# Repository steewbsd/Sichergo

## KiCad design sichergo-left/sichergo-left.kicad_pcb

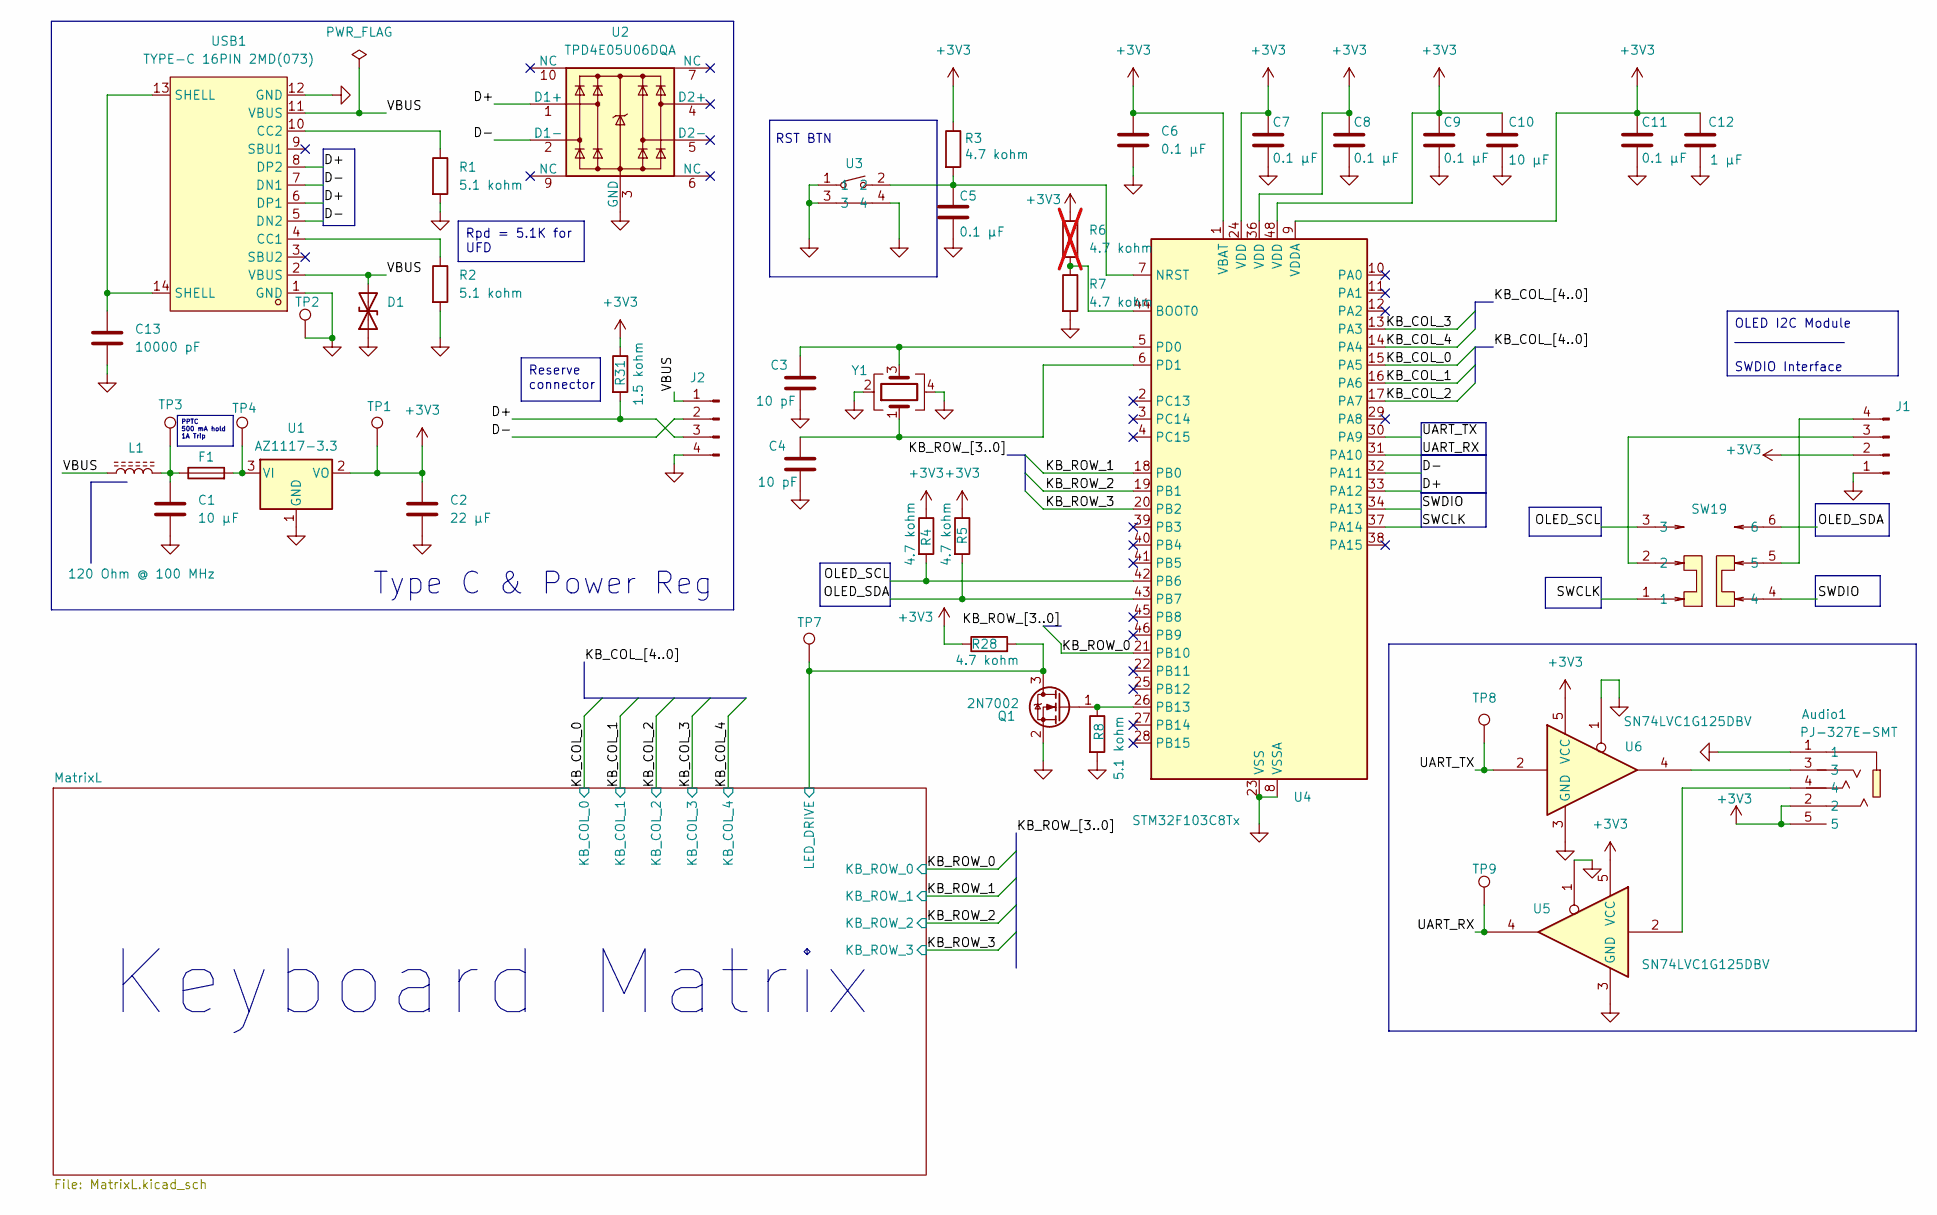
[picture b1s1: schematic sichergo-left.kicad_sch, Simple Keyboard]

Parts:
Audio1: PJ-327E-SMT; AUDIO-SMD_PJ-327E-SMT; LCSC Part C319105
C1, C10: 10 µF; C_0805_2012Metric_Pad1.18x1.45mm_HandSolder; Rated Voltage 16V; Tolerance 10%
C2: 22 µF; C_0805_2012Metric_Pad1.18x1.45mm_HandSolder; Rated Voltage 16V; Tolerance 20%
C3, C4: 10 pF; C_0805_2012Metric_Pad1.18x1.45mm_HandSolder; Rated Voltage 50V; Tolerance 0.25pF
C5, C6, C7, C8, C9, C11: 0.1 µF; C_0805_2012Metric_Pad1.18x1.45mm_HandSolder; Rated Voltage 50V; Tolerance 10%
C12: 1 µF; C_0805_2012Metric_Pad1.18x1.45mm_HandSolder; Rated Voltage 25V; Tolerance 10%
C13: 10000 pF; C_0805_2012Metric_Pad1.18x1.45mm_HandSolder; Rated Voltage 50V; Tolerance 10%
D1: CPDUR5V0HE-HF; D_0603_1608Metric_Pad1.05x0.95mm_HandSolder
F1: 1812L050/30PR; Fuse_1812_4532Metric_Pad1.30x3.40mm_HandSolder
J1: Conn_01x04_Pin; PinSocket_1x04_P2.54mm_Horizontal
J2: Conn_01x04_Pin; PinSocket_1x04_P2.54mm_Vertical
L1: 120 Ohm @ 100 MHz; L_0603_1608Metric_Pad1.05x0.95mm_HandSolder
Q1: 2N7002; SOT-23_Handsoldering
R1, R2, R8: 5.1 kohm; R_0603_1608Metric_Pad0.98x0.95mm_HandSolder; Tolerance 1%
R3, R4, R5, R7, R28: 4.7 kohm; R_0603_1608Metric_Pad0.98x0.95mm_HandSolder; Tolerance 1%
R6: 4.7 kohm; R_0603_1608Metric_Pad0.98x0.95mm_HandSolder; Tolerance 1%; not fitted
R31: 1.5 kohm; R_0603_1608Metric_Pad0.98x0.95mm_HandSolder; Tolerance 1%
SW19: MS-22C01-G010; SW-SMD_6P-L7.2-W3.5-P2.50-LS6.0-TL; LCSC Part C2837066
TP1, TP2, TP3, TP4, TP7, TP8, TP9: TestPoint; TestPoint_THTPad_1.0x1.0mm_Drill0.5mm
U1: AZ1117-3.3; SOT-223-3_TabPin2
U2: TPD4E05U06DQA; USON-10_2.5x1.0mm_P0.5mm
U3: YTS1C0033BBG01; SW-SMD_YIYUAN_YTS1C003XXX; LCSC Part C5188566
U4: STM32F103C8Tx; LQFP-48_7x7mm_P0.5mm
U5, U6: SN74LVC1G125DBV; SOT-23-5_HandSoldering
USB1: TYPE-C 16PIN 2MD(073); USB-C-SMD_TYPE-C-6PIN-2MD-073; LCSC Part C2765186
Y1: Crystal_GND24; Crystal_SMD_3225-4Pin_3.2x2.5mm_HandSoldering

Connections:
+3V3: Audio1.2, Audio1.5, C2.1, C6.1, C7.1, C8.1, C9.1, C10.1, C11.1, C12.1, J1.2, R3.1, R4.1, R5.1, R6.1, R28.1, R31.1, TP1.1, U1.2 (VO), U4.1 (VBAT), U4.9 (VDDA), U4.24 (VDD), U4.36 (VDD), U4.48 (VDD), U5.5 (VCC), U6.5 (VCC)
/D+: J2.3, R31.2, U2.1 (D1+), U4.33 (PA12), USB1.6 (DP1), USB1.8 (DP2)
/D-: J2.2, U2.2 (D1-), U4.32 (PA11), USB1.5 (DN2), USB1.7 (DN1)
/KB_COL_0: U4.15 (PA5); also elsewhere on the board
/KB_COL_1: U4.16 (PA6); also elsewhere on the board
/KB_COL_2: U4.17 (PA7); also elsewhere on the board
/KB_COL_3: U4.13 (PA3); also elsewhere on the board
/KB_COL_4: U4.14 (PA4); also elsewhere on the board
/KB_ROW_0: U4.21 (PB10); also elsewhere on the board
/KB_ROW_1: U4.18 (PB0); also elsewhere on the board
/KB_ROW_2: U4.19 (PB1); also elsewhere on the board
/KB_ROW_3: U4.20 (PB2); also elsewhere on the board
/MatrixL/LED_DRIVE: Q1.3 (D), R28.2, TP7.1; also elsewhere on the board
/OLED_SCL: R4.2, SW19.3, U4.42 (PB6)
/OLED_SDA: R5.2, SW19.6, U4.43 (PB7)
/SWCLK: SW19.1, U4.37 (PA14)
/SWDIO: SW19.4, U4.34 (PA13)
/UART_RX: TP9.1, U4.31 (PA10), U5.4
/UART_TX: TP8.1, U4.30 (PA9), U6.2
/VBUS: D1.2 (A2), J2.1, L1.1, USB1.2 (VBUS), USB1.11 (VBUS)
GND: Audio1.1, C1.2, C2.2, C3.2, C4.2, C5.2, C6.2, C7.2, C8.2, C9.2, C10.2, C11.2, C12.2, C13.2, D1.1 (A1), J1.1, J2.4, Q1.2 (S), R1.2, R2.2, R7.2, R8.2, TP2.1, U1.1 (GND), U2.3 (GND), U2.8 (GND), U3.1, U3.3, U3.4, U4.8 (VSSA), U4.23 (VSS), U4.35 (VSS), U4.47 (VSS), U5.1, U5.3 (GND), U6.1, U6.3 (GND), USB1.1 (GND), USB1.12 (GND), Y1.2, Y1.4; also elsewhere on the board
unnamed: Audio1.3, U6.4
unnamed: Audio1.4, U5.2
unnamed: C1.1, F1.1, L1.2, TP3.1
unnamed: C13.1, USB1.13 (SHELL), USB1.14 (SHELL)
unnamed: J1.3, SW19.2
unnamed: J1.4, SW19.5
unnamed: Q1.1 (G), R8.1, U4.26 (PB13)
unnamed: F1.2, TP4.1, U1.3 (VI)
unnamed: R6.2, R7.1, U4.44 (BOOT0)
unnamed: C5.1, R3.2, U3.2, U4.7 (NRST)
unnamed: C3.1, U4.5 (PD0), Y1.3
unnamed: C4.1, U4.6 (PD1), Y1.1
unnamed: R2.1, USB1.4 (CC1)
unnamed: R1.1, USB1.10 (CC2)

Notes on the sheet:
RST BTN
Keyboard Matrix
Type C & Power Reg
PPTC 500 mA hold 1A Trip
Rpd = 5.1K for UFD
OLED I2C Module ________________ SWDIO Interface
Reserve connector

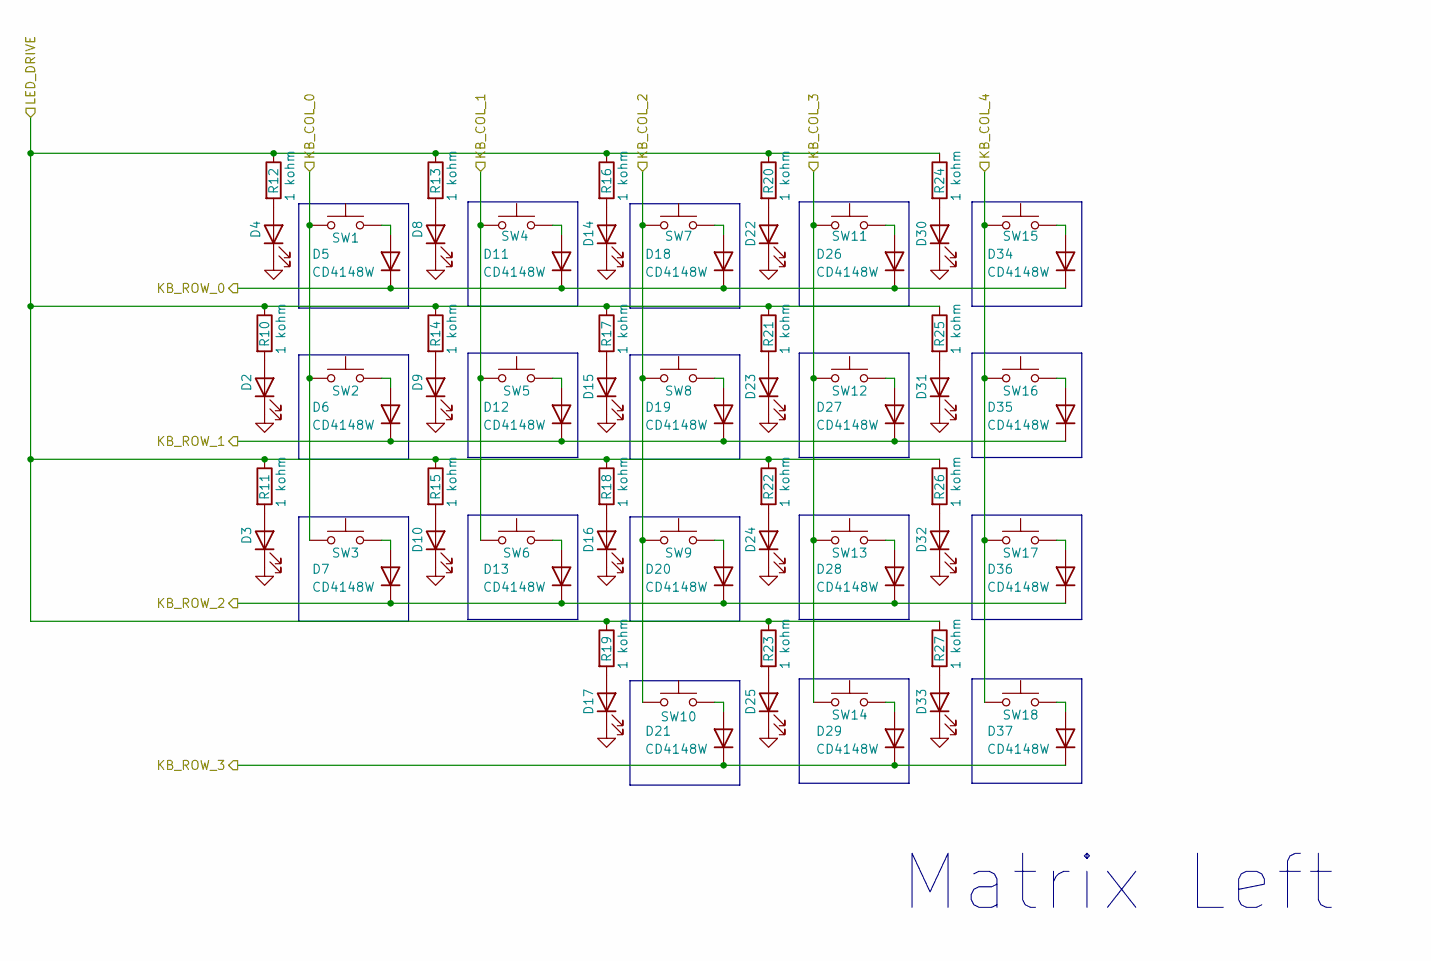
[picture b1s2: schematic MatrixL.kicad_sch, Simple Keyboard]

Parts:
D2, D3, D4, D8, D9, D10, D14, D15, D16, D17, D22, D23, D24, D25, D30, D31, D32, D33: LED; LED_0603_1608Metric_Pad1.05x0.95mm_HandSolder
D5, D6, D7, D11, D12, D13, D18, D19, D20, D21, D26, D27, D28, D29, D34, D35, D36, D37: CD4148W; D_0805_2012Metric_Pad1.15x1.40mm_HandSolder
R10, R11, R12, R13, R14, R15, R16, R17, R18, R19, R20, R21, R22, R23, R24, R25, R26, R27: 1 kohm; R_0603_1608Metric_Pad0.98x0.95mm_HandSolder; Tolerance 1%
SW1, SW2, SW3, SW4, SW5, SW6, SW7, SW8, SW9, SW10, SW11, SW12, SW13, SW14, SW15, SW16, SW17, SW18: SW_Push; Gateron_Milky_Yellow

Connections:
/KB_COL_0: SW1.1, SW2.1, SW3.1; also elsewhere on the board
/KB_COL_1: SW4.1, SW5.1, SW6.1; also elsewhere on the board
/KB_COL_2: SW7.1, SW8.1, SW9.1, SW10.1; also elsewhere on the board
/KB_COL_3: SW11.1, SW12.1, SW13.1, SW14.1; also elsewhere on the board
/KB_COL_4: SW15.1, SW16.1, SW17.1, SW18.1; also elsewhere on the board
/KB_ROW_0: D5.1 (K), D11.1 (K), D18.1 (K), D26.1 (K), D34.1 (K); also elsewhere on the board
/KB_ROW_1: D6.1 (K), D12.1 (K), D19.1 (K), D27.1 (K), D35.1 (K); also elsewhere on the board
/KB_ROW_2: D7.1 (K), D13.1 (K), D20.1 (K), D28.1 (K), D36.1 (K); also elsewhere on the board
/KB_ROW_3: D21.1 (K), D29.1 (K), D37.1 (K); also elsewhere on the board
/MatrixL/LED_DRIVE: R10.1, R11.1, R12.1, R13.1, R14.1, R15.1, R16.1, R17.1, R18.1, R19.1, R20.1, R21.1, R22.1, R23.1, R24.1, R25.1, R26.1, R27.1; also elsewhere on the board
GND: D2.1 (K), D3.1 (K), D4.1 (K), D8.1 (K), D9.1 (K), D10.1 (K), D14.1 (K), D15.1 (K), D16.1 (K), D17.1 (K), D22.1 (K), D23.1 (K), D24.1 (K), D25.1 (K), D30.1 (K), D31.1 (K), D32.1 (K), D33.1 (K); also elsewhere on the board
unnamed: D2.2 (A), R10.2
unnamed: D3.2 (A), R11.2
unnamed: D4.2 (A), R12.2
unnamed: D5.2 (A), SW1.2
unnamed: D6.2 (A), SW2.2
unnamed: D7.2 (A), SW3.2
unnamed: D8.2 (A), R13.2
unnamed: D9.2 (A), R14.2
unnamed: D10.2 (A), R15.2
unnamed: D11.2 (A), SW4.2
unnamed: D12.2 (A), SW5.2
unnamed: D13.2 (A), SW6.2
unnamed: D14.2 (A), R16.2
unnamed: D15.2 (A), R17.2
unnamed: D16.2 (A), R18.2
unnamed: D17.2 (A), R19.2
unnamed: D18.2 (A), SW7.2
unnamed: D19.2 (A), SW8.2
unnamed: D20.2 (A), SW9.2
unnamed: D21.2 (A), SW10.2
unnamed: D22.2 (A), R20.2
unnamed: D23.2 (A), R21.2
unnamed: D24.2 (A), R22.2
unnamed: D25.2 (A), R23.2
unnamed: D26.2 (A), SW11.2
unnamed: D27.2 (A), SW12.2
unnamed: D28.2 (A), SW13.2
unnamed: D29.2 (A), SW14.2
unnamed: D30.2 (A), R24.2
unnamed: D31.2 (A), R25.2
unnamed: D32.2 (A), R26.2
unnamed: D33.2 (A), R27.2
unnamed: D34.2 (A), SW15.2
unnamed: D35.2 (A), SW16.2
unnamed: D36.2 (A), SW17.2
unnamed: D37.2 (A), SW18.2

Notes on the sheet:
Matrix Left

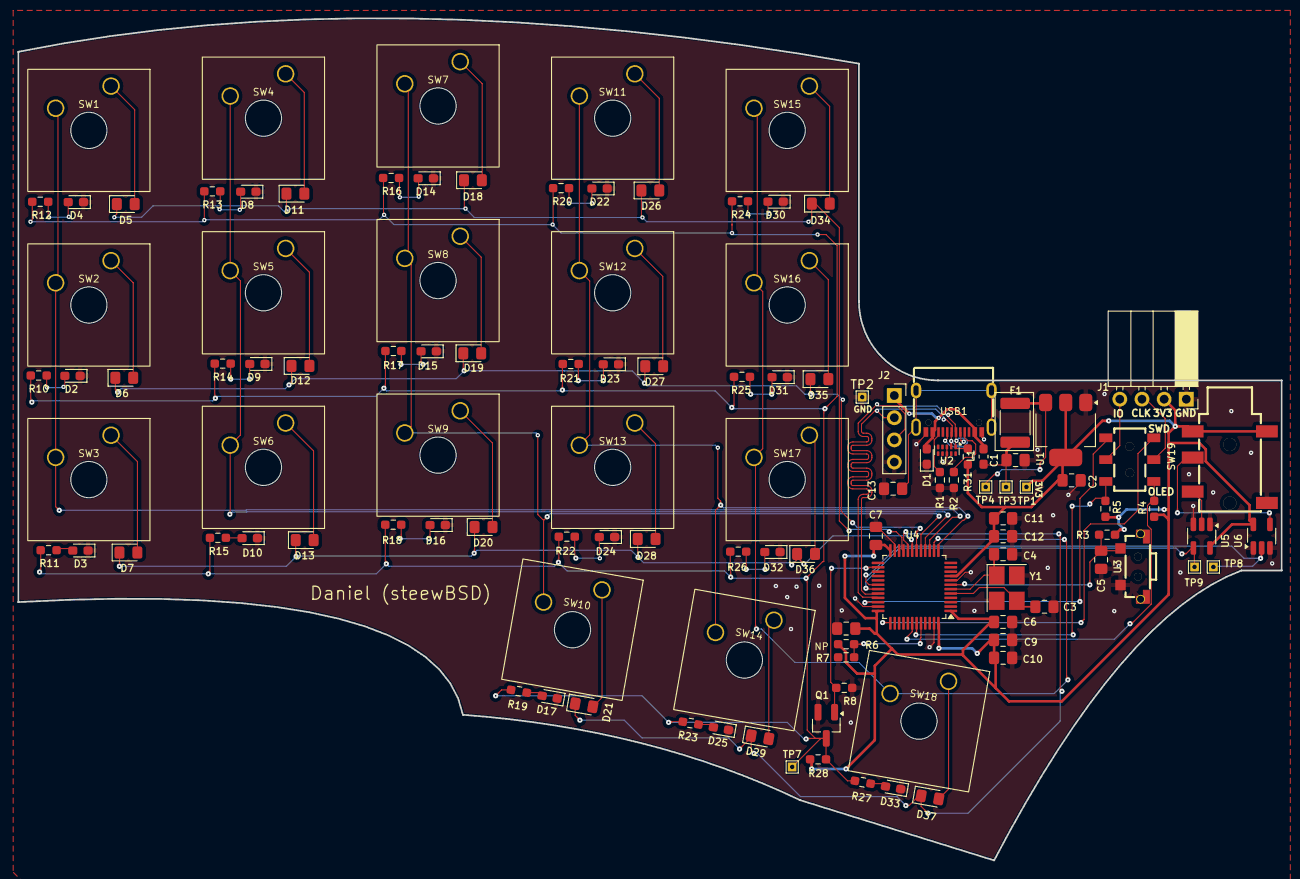
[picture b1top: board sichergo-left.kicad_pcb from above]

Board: 2 copper layers, 144.7 x 96.5 mm, 118 parts (0 on the bottom side), 71 nets.

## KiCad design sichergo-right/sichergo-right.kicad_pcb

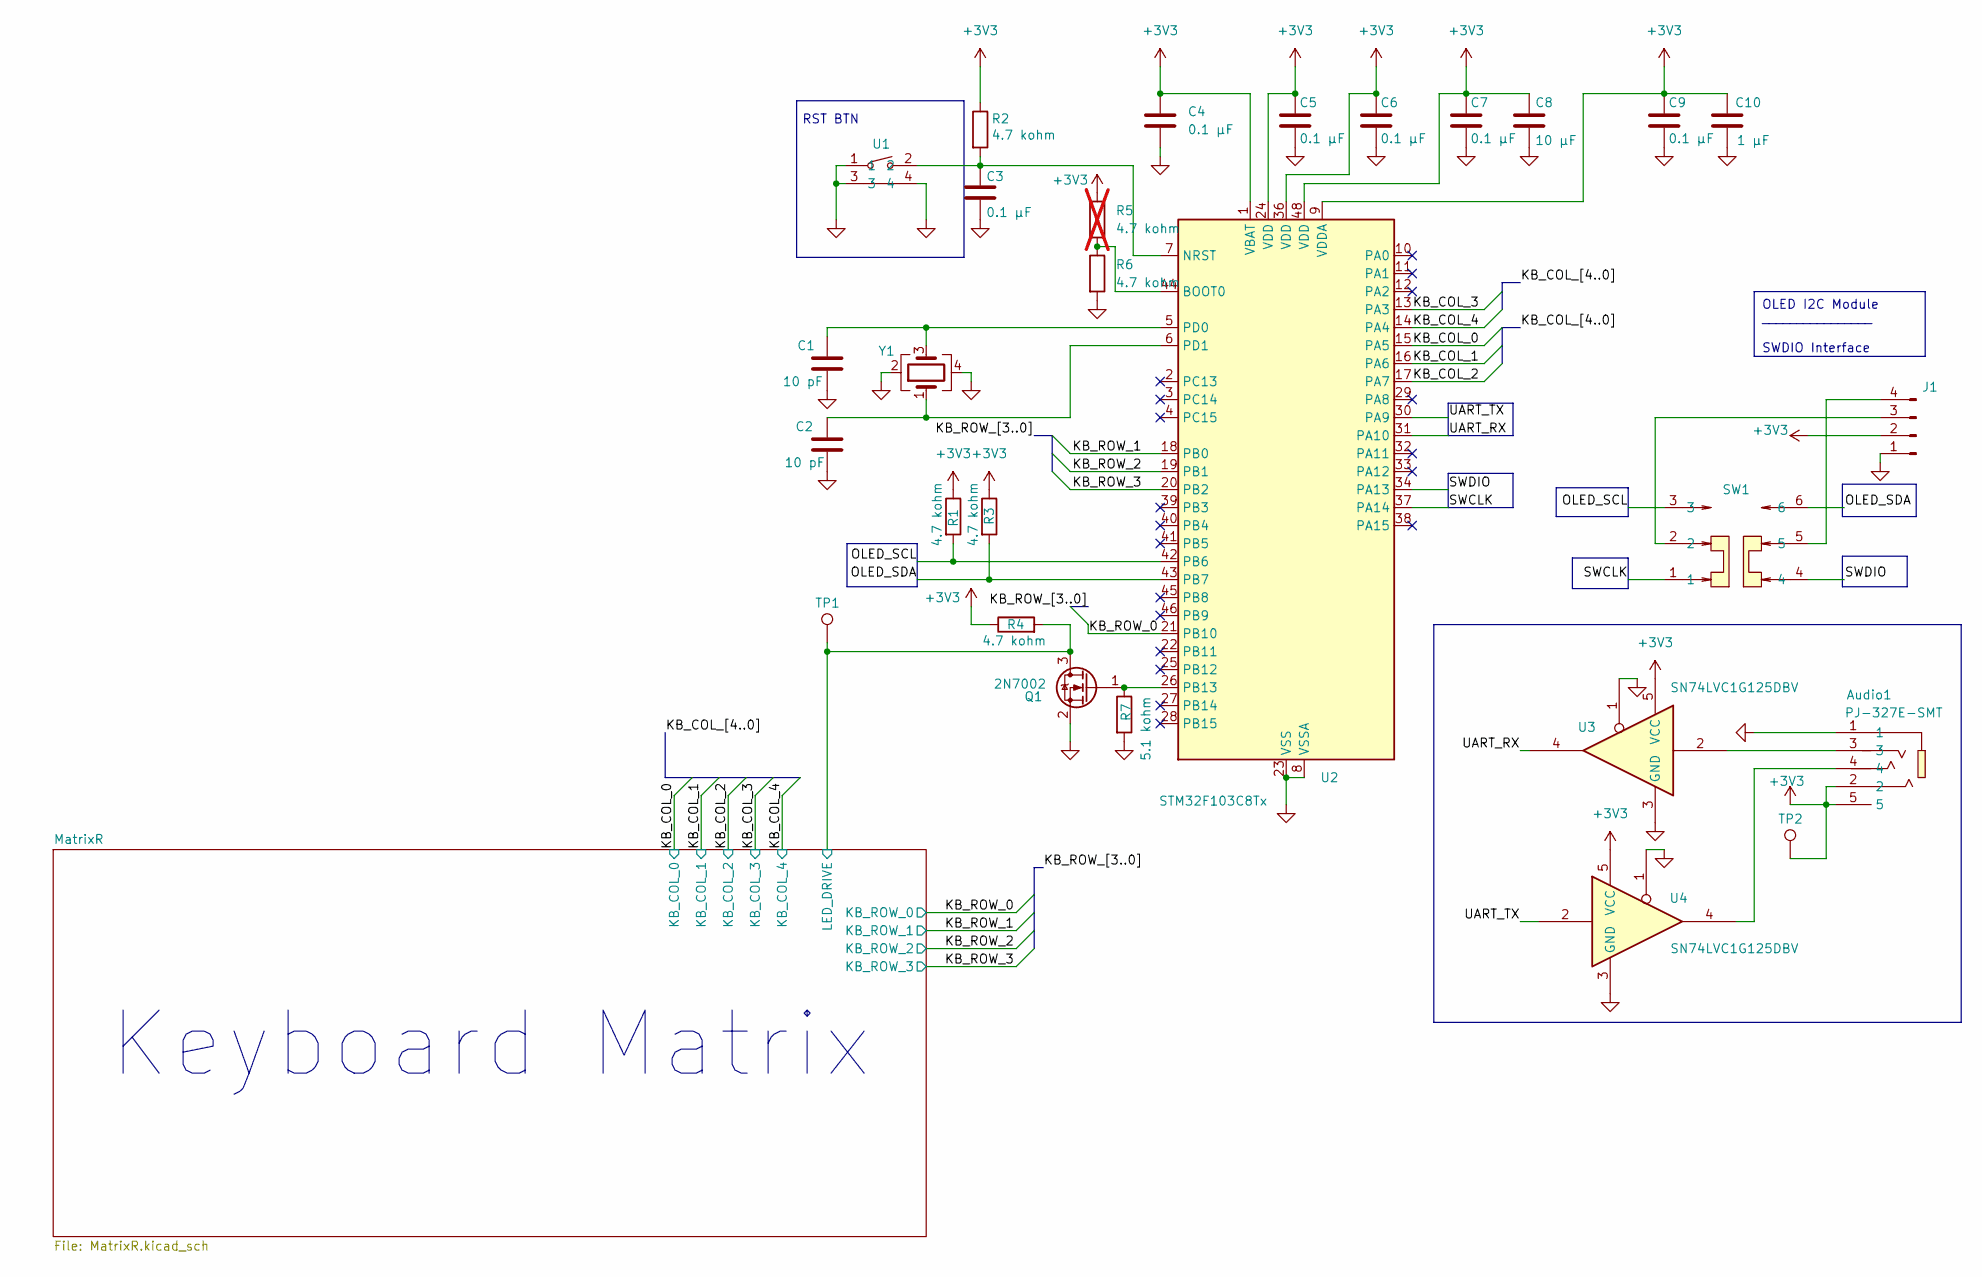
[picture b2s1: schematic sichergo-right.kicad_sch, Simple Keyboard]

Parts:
Audio1: PJ-327E-SMT; AUDIO-SMD_PJ-327E-SMT; LCSC Part C319105
C1, C2: 10 pF; C_0805_2012Metric_Pad1.18x1.45mm_HandSolder; Rated Voltage 50V; Tolerance 0.25pF
C3, C4, C5, C6, C7, C9: 0.1 µF; C_0805_2012Metric_Pad1.18x1.45mm_HandSolder; Rated Voltage 50V; Tolerance 10%
C8: 10 µF; C_0805_2012Metric_Pad1.18x1.45mm_HandSolder; Rated Voltage 16V; Tolerance 10%
C10: 1 µF; C_0805_2012Metric_Pad1.18x1.45mm_HandSolder; Rated Voltage 25V; Tolerance 10%
J1: Conn_01x04_Pin; PinSocket_1x04_P2.54mm_Horizontal
Q1: 2N7002; SOT-23_Handsoldering
R1, R2, R3, R4, R6: 4.7 kohm; R_0603_1608Metric_Pad0.98x0.95mm_HandSolder; Tolerance 1%
R5: 4.7 kohm; R_0603_1608Metric_Pad0.98x0.95mm_HandSolder; Tolerance 1%; not fitted
R7: 5.1 kohm; R_0603_1608Metric_Pad0.98x0.95mm_HandSolder; Tolerance 1%
SW1: MS-22C01-G010; SW-SMD_6P-L7.2-W3.5-P2.50-LS6.0-TL; LCSC Part C2837066
TP1, TP2: TestPoint; TestPoint_THTPad_1.0x1.0mm_Drill0.5mm
U1: YTS1C0033BBG01; SW-SMD_YIYUAN_YTS1C003XXX; LCSC Part C5188566
U2: STM32F103C8Tx; LQFP-48_7x7mm_P0.5mm
U3, U4: SN74LVC1G125DBV; SOT-23-5_HandSoldering
Y1: Crystal_GND24; Crystal_SMD_3225-4Pin_3.2x2.5mm_HandSoldering

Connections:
+3V3: Audio1.2, Audio1.5, C4.1, C5.1, C6.1, C7.1, C8.1, C9.1, C10.1, J1.2, R1.1, R2.1, R3.1, R4.1, R5.1, TP2.1, U2.1 (VBAT), U2.9 (VDDA), U2.24 (VDD), U2.36 (VDD), U2.48 (VDD), U3.5 (VCC), U4.5 (VCC)
/KB_COL_0: U2.15 (PA5); also elsewhere on the board
/KB_COL_1: U2.16 (PA6); also elsewhere on the board
/KB_COL_2: U2.17 (PA7); also elsewhere on the board
/KB_COL_3: U2.13 (PA3); also elsewhere on the board
/KB_COL_4: U2.14 (PA4); also elsewhere on the board
/KB_ROW_0: U2.21 (PB10); also elsewhere on the board
/KB_ROW_1: U2.18 (PB0); also elsewhere on the board
/KB_ROW_2: U2.19 (PB1); also elsewhere on the board
/KB_ROW_3: U2.20 (PB2); also elsewhere on the board
/MatrixR/LED_DRIVE: Q1.3 (D), R4.2, TP1.1; also elsewhere on the board
/OLED_SCL: R1.2, SW1.3, U2.42 (PB6)
/OLED_SDA: R3.2, SW1.6, U2.43 (PB7)
/SWCLK: SW1.1, U2.37 (PA14)
/SWDIO: SW1.4, U2.34 (PA13)
/UART_RX: U2.31 (PA10), U3.4
/UART_TX: U2.30 (PA9), U4.2
GND: Audio1.1, C1.2, C2.2, C3.2, C4.2, C5.2, C6.2, C7.2, C8.2, C9.2, C10.2, J1.1, Q1.2 (S), R6.2, R7.2, U1.1, U1.3, U1.4, U2.8 (VSSA), U2.23 (VSS), U2.35 (VSS), U2.47 (VSS), U3.1, U3.3 (GND), U4.1, U4.3 (GND), Y1.2, Y1.4; also elsewhere on the board
unnamed: Audio1.3, U3.2
unnamed: Audio1.4, U4.4
unnamed: J1.3, SW1.2
unnamed: J1.4, SW1.5
unnamed: Q1.1 (G), R7.1, U2.26 (PB13)
unnamed: R5.2, R6.1, U2.44 (BOOT0)
unnamed: C3.1, R2.2, U1.2, U2.7 (NRST)
unnamed: C1.1, U2.5 (PD0), Y1.3
unnamed: C2.1, U2.6 (PD1), Y1.1

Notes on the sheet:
OLED I2C Module ________________ SWDIO Interface
RST BTN
Keyboard Matrix

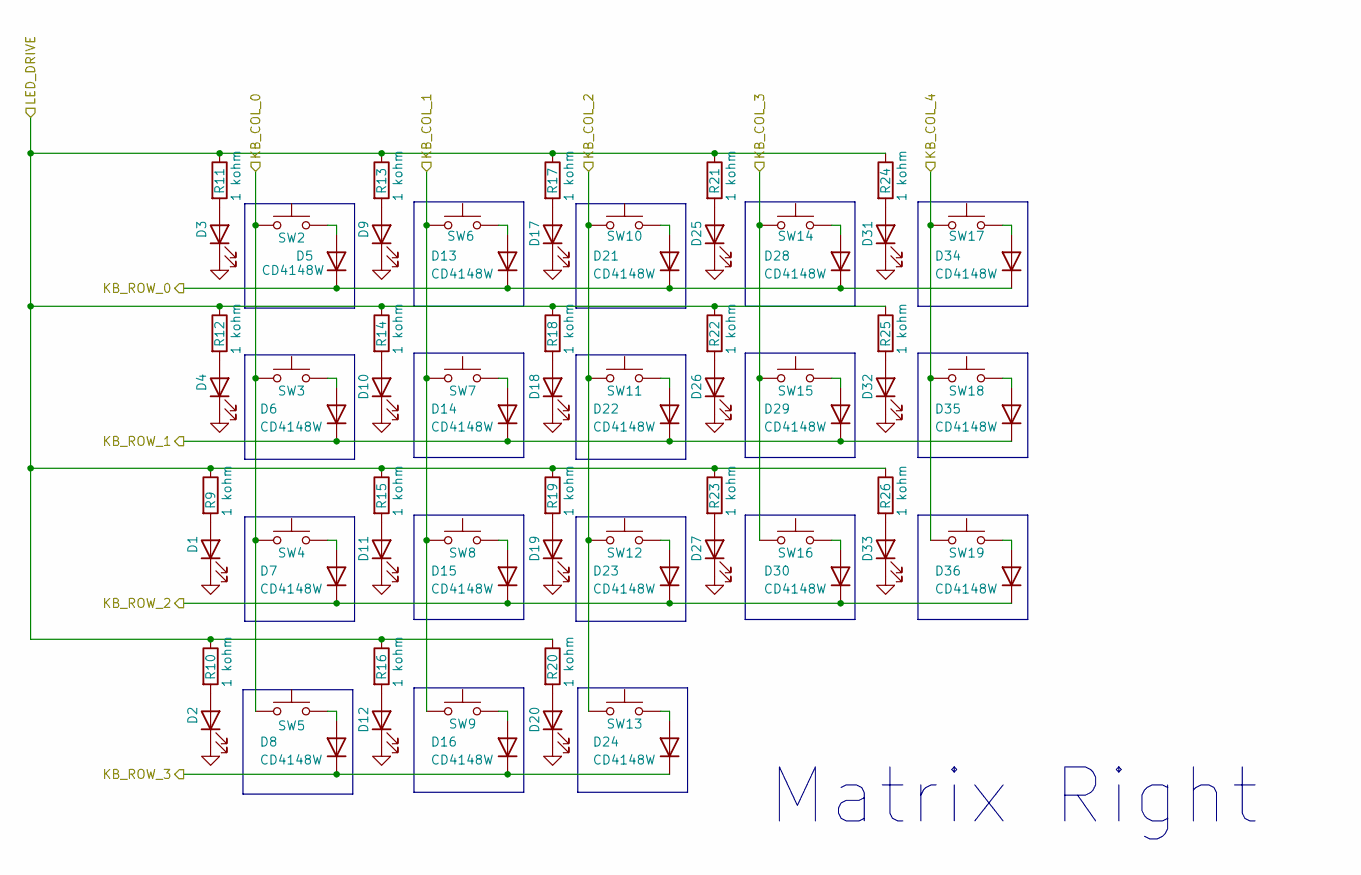
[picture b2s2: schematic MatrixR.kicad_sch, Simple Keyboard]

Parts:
D1, D2, D3, D4, D9, D10, D11, D12, D17, D18, D19, D20, D25, D26, D27, D31, D32, D33: LED; LED_0603_1608Metric_Pad1.05x0.95mm_HandSolder
D5, D6, D7, D8, D13, D14, D15, D16, D21, D22, D23, D24, D28, D29, D30, D34, D35, D36: CD4148W; D_0805_2012Metric_Pad1.15x1.40mm_HandSolder
R9, R10, R11, R12, R13, R14, R15, R16, R17, R18, R19, R20, R21, R22, R23, R24, R25, R26: 1 kohm; R_0603_1608Metric_Pad0.98x0.95mm_HandSolder; Tolerance 1%
SW2, SW3, SW4, SW5, SW6, SW7, SW8, SW9, SW10, SW11, SW12, SW13, SW14, SW15, SW16, SW17, SW18, SW19: SW_Push; Gateron_Milky_Yellow

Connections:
/KB_COL_0: SW2.1, SW3.1, SW4.1, SW5.1; also elsewhere on the board
/KB_COL_1: SW6.1, SW7.1, SW8.1, SW9.1; also elsewhere on the board
/KB_COL_2: SW10.1, SW11.1, SW12.1, SW13.1; also elsewhere on the board
/KB_COL_3: SW14.1, SW15.1, SW16.1; also elsewhere on the board
/KB_COL_4: SW17.1, SW18.1, SW19.1; also elsewhere on the board
/KB_ROW_0: D5.1 (K), D13.1 (K), D21.1 (K), D28.1 (K), D34.1 (K); also elsewhere on the board
/KB_ROW_1: D6.1 (K), D14.1 (K), D22.1 (K), D29.1 (K), D35.1 (K); also elsewhere on the board
/KB_ROW_2: D7.1 (K), D15.1 (K), D23.1 (K), D30.1 (K), D36.1 (K); also elsewhere on the board
/KB_ROW_3: D8.1 (K), D16.1 (K), D24.1 (K); also elsewhere on the board
/MatrixR/LED_DRIVE: R9.1, R10.1, R11.1, R12.1, R13.1, R14.1, R15.1, R16.1, R17.1, R18.1, R19.1, R20.1, R21.1, R22.1, R23.1, R24.1, R25.1, R26.1; also elsewhere on the board
GND: D1.1 (K), D2.1 (K), D3.1 (K), D4.1 (K), D9.1 (K), D10.1 (K), D11.1 (K), D12.1 (K), D17.1 (K), D18.1 (K), D19.1 (K), D20.1 (K), D25.1 (K), D26.1 (K), D27.1 (K), D31.1 (K), D32.1 (K), D33.1 (K); also elsewhere on the board
unnamed: D1.2 (A), R9.2
unnamed: D2.2 (A), R10.2
unnamed: D3.2 (A), R11.2
unnamed: D4.2 (A), R12.2
unnamed: D5.2 (A), SW2.2
unnamed: D6.2 (A), SW3.2
unnamed: D7.2 (A), SW4.2
unnamed: D8.2 (A), SW5.2
unnamed: D9.2 (A), R13.2
unnamed: D10.2 (A), R14.2
unnamed: D11.2 (A), R15.2
unnamed: D12.2 (A), R16.2
unnamed: D13.2 (A), SW6.2
unnamed: D14.2 (A), SW7.2
unnamed: D15.2 (A), SW8.2
unnamed: D16.2 (A), SW9.2
unnamed: D17.2 (A), R17.2
unnamed: D18.2 (A), R18.2
unnamed: D19.2 (A), R19.2
unnamed: D20.2 (A), R20.2
unnamed: D21.2 (A), SW10.2
unnamed: D22.2 (A), SW11.2
unnamed: D23.2 (A), SW12.2
unnamed: D24.2 (A), SW13.2
unnamed: D25.2 (A), R21.2
unnamed: D26.2 (A), R22.2
unnamed: D27.2 (A), R23.2
unnamed: D28.2 (A), SW14.2
unnamed: D29.2 (A), SW15.2
unnamed: D30.2 (A), SW16.2
unnamed: D31.2 (A), R24.2
unnamed: D32.2 (A), R25.2
unnamed: D33.2 (A), R26.2
unnamed: D34.2 (A), SW17.2
unnamed: D35.2 (A), SW18.2
unnamed: D36.2 (A), SW19.2

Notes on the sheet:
Matrix Right

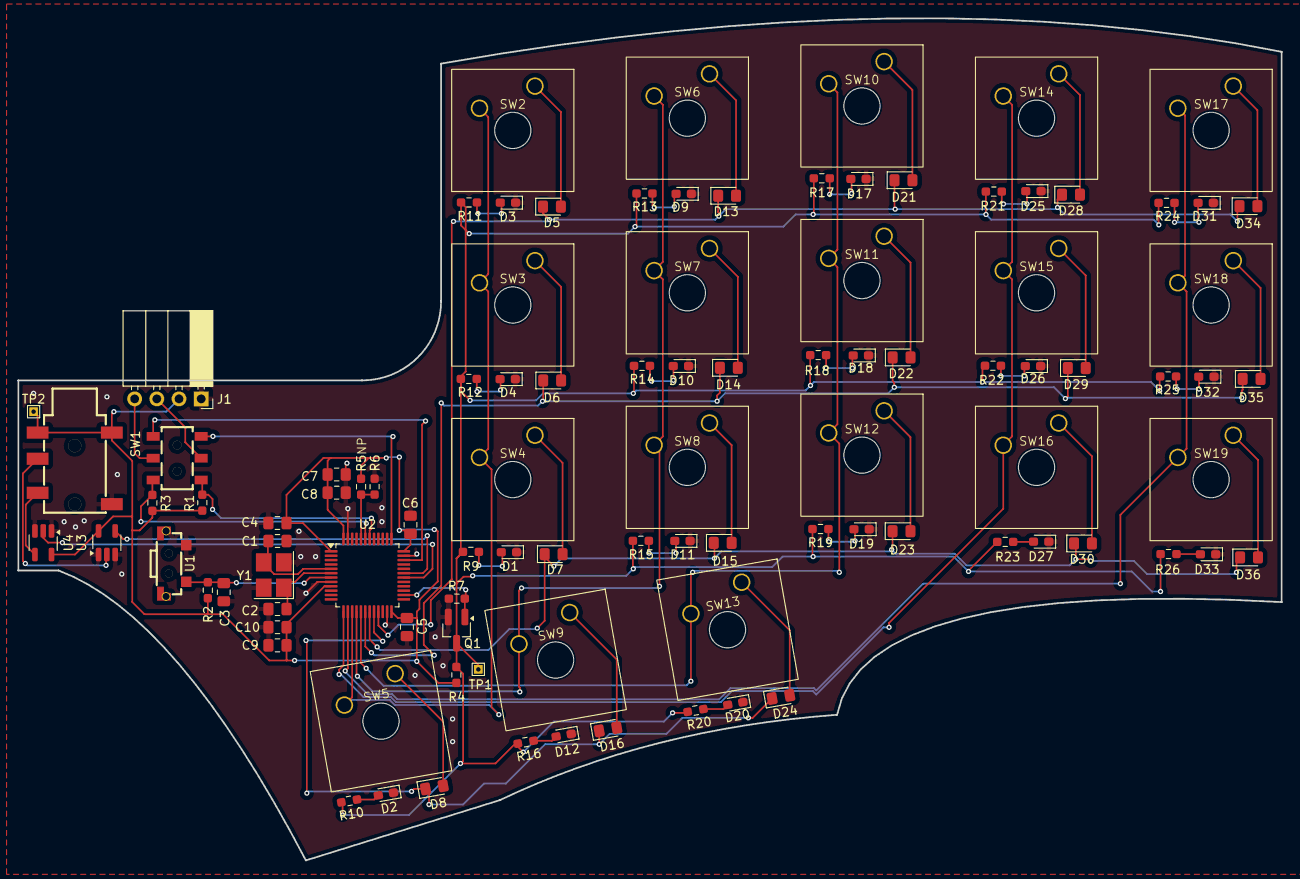
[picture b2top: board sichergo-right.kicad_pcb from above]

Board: 2 copper layers, 144.7 x 96.5 mm, 100 parts (0 on the bottom side), 63 nets.

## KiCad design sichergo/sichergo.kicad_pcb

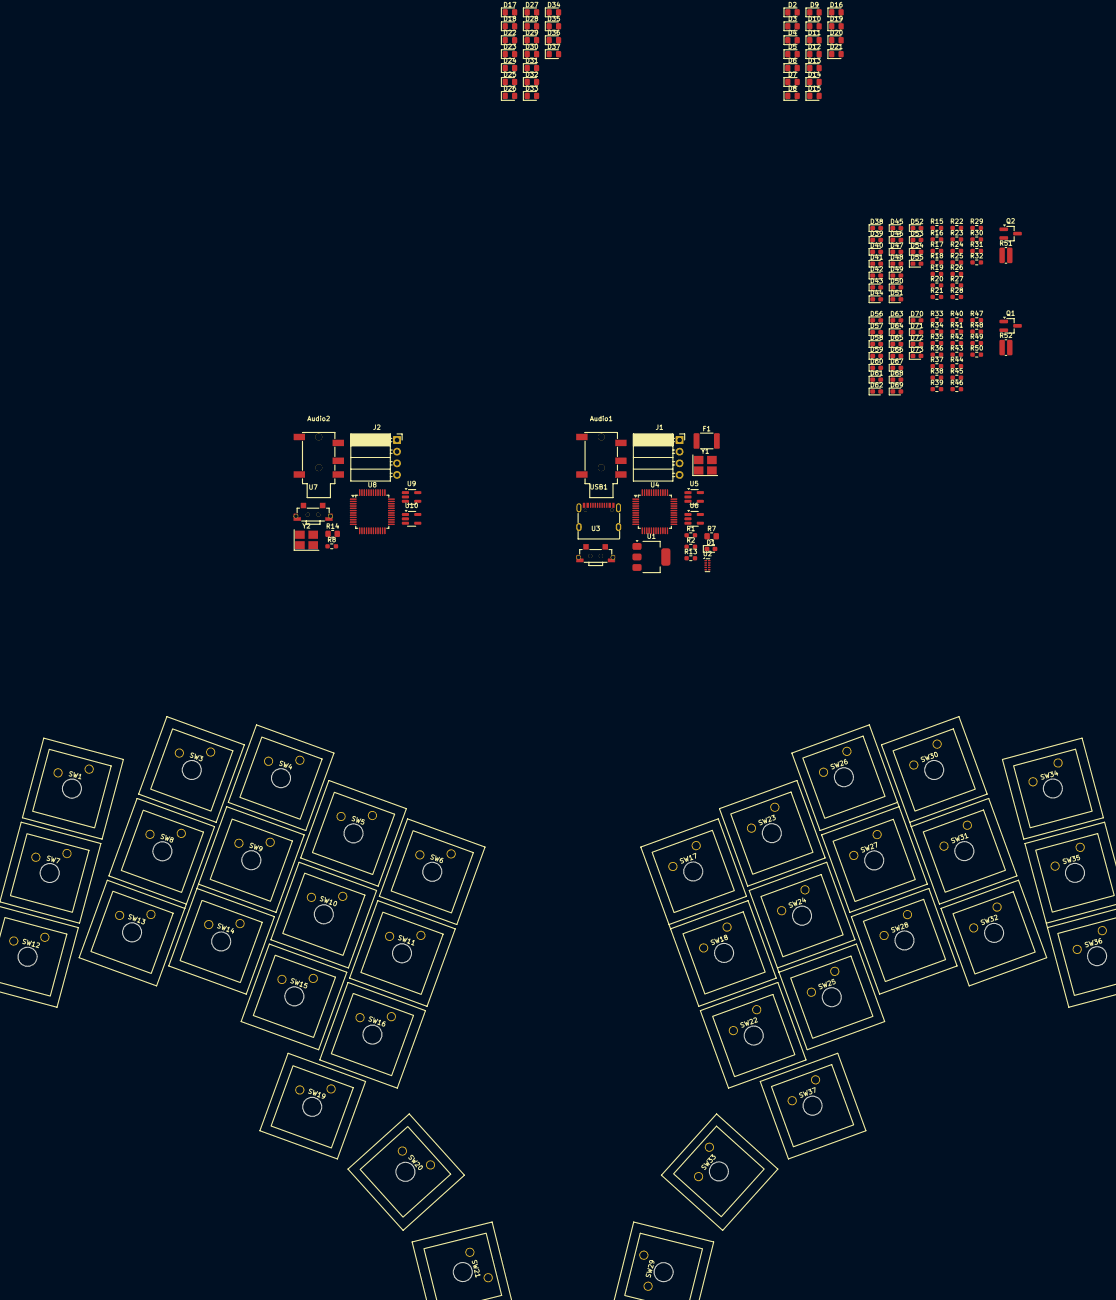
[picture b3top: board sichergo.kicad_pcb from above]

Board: 2 copper layers, 173 parts (0 on the bottom side), 116 nets, no tracks yet.

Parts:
Audio1, Audio2: PJ-327E-SMT; AUDIO-SMD_PJ-327E-SMT
D1: CPDUR5V0HE-HF; D_0603_1608Metric_Pad1.05x0.95mm_HandSolder
D2, D3, D4, D5, D6, D7, D8, D9, D10, D11, D12, D13, D14, D15, D16, D17, D18, D19, D20, D21, D22, D23, D24, D25, D26, D27, D28, D29, D30, D31, D32, D33, D34, D35, D36, D37: CD4148W; D_0805_2012Metric_Pad1.15x1.40mm_HandSolder
D38, D39, D40, D41, D42, D43, D44, D45, D46, D47, D48, D49, D50, D51, D52, D53, D54, D55, D56, D57, D58, D59, D60, D61, D62, D63, D64, D65, D66, D67, D68, D69, D70, D71, D72, D73: LED; LED_0603_1608Metric_Pad1.05x0.95mm_HandSolder
F1: 1812L050/30PR; Fuse_1812_4532Metric_Pad1.30x3.40mm_HandSolder
J1, J2: Conn_01x04_Pin; PinSocket_1x04_P2.54mm_Horizontal
Q1, Q2: 2N7002; SOT-23_Handsoldering
R1, R13: 5.1 kohm; R_0603_1608Metric_Pad0.98x0.95mm_HandSolder
R2, R8: 4.7 kohm; R_0603_1608Metric_Pad0.98x0.95mm_HandSolder
R7, R14: 100 ohm; R_0805_2012Metric_Pad1.20x1.40mm_HandSolder
R15, R16, R17, R18, R19, R20, R21, R22, R23, R24, R25, R26, R27, R28, R29, R30, R31, R32, R33, R34, R35, R36, R37, R38, R39, R40, R41, R42, R43, R44, R45, R46, R47, R48, R49, R50: 1 kohm; R_0603_1608Metric_Pad0.98x0.95mm_HandSolder
R51, R52: 5.1 kohm; R_0612_1632Metric_Pad1.18x3.40mm_HandSolder
SW1, SW3, SW4, SW5, SW6, SW7, SW8, SW9, SW10, SW11, SW12, SW13, SW14, SW15, SW16, SW17, SW18, SW19, SW20, SW21, SW22, SW23, SW24, SW25, SW26, SW27, SW28, SW29, SW30, SW31, SW32, SW33, SW34, SW35, SW36, SW37: SW_Push; Gateron_Milky_Yellow
U1: AZ1117-3.3; SOT-223-3_TabPin2
U2: TPD4E05U06DQA; USON-10_2.5x1.0mm_P0.5mm
U3, U7: YTS1C0033BBG01; SW-SMD_YIYUAN_YTS1C003XXX
U4, U8: STM32F103C8Tx; LQFP-48_7x7mm_P0.5mm
U5, U6, U9, U10: SN74LVC1G125DBV; SOT-23-5_HandSoldering
USB1: TYPE-C 16PIN 2MD(073); USB-C-SMD_TYPE-C-6PIN-2MD-073
Y1, Y2: Crystal_GND24; Crystal_SMD_3225-4Pin_3.2x2.5mm_HandSoldering

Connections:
+3V3: Audio1.2, Audio1.5, Audio2.2, Audio2.5, J1.2, J2.2, Q1.3 (D), Q2.3 (D), R2.1, R8.1, R15.1, R16.1, R17.1, R18.1, R19.1, R20.1, R21.1, R22.1, R23.1, R24.1, R25.1, R26.1, R27.1, R28.1, R29.1, R30.1, R31.1, R32.1, R33.1, R34.1, R35.1, R36.1, R37.1, R38.1, R39.1, R40.1, R41.1, R42.1, R43.1, R44.1, R45.1, R46.1, R47.1, R48.1, R49.1, R50.1, U1.2 (VO), U4.1 (VBAT), U4.9 (VDDA), U4.24 (VDD), U4.36 (VDD), U4.48 (VDD), U5.5 (VCC), U6.5 (VCC), U8.1 (VBAT), U8.9 (VDDA), U8.24 (VDD), U8.36 (VDD), U8.48 (VDD), U9.5 (VCC), U10.5 (VCC)
/KBD_L/D+: U2.1 (D1+), USB1.6 (DP1), USB1.8 (DP2)
/KBD_L/D-: U2.2 (D1-), USB1.5 (DN2), USB1.7 (DN1)
/KBD_L/KB_COL_0: SW1.1, SW7.1, SW12.1, U4.10 (PA0)
/KBD_L/KB_COL_1: SW3.1, SW8.1, SW13.1, U4.11 (PA1)
/KBD_L/KB_COL_2: SW4.1, SW9.1, SW14.1, SW19.1, U4.12 (PA2)
/KBD_L/KB_COL_3: SW5.1, SW10.1, SW15.1, SW20.1, U4.13 (PA3)
/KBD_L/KB_COL_4: SW6.1, SW11.1, SW16.1, SW21.1, U4.14 (PA4)
/KBD_L/KB_ROW_0: D2.1 (K), D3.1 (K), D4.1 (K), D5.1 (K), D6.1 (K), U4.15 (PA5)
/KBD_L/KB_ROW_1: D7.1 (K), D8.1 (K), D9.1 (K), D10.1 (K), D11.1 (K), U4.16 (PA6)
/KBD_L/KB_ROW_2: D12.1 (K), D13.1 (K), D14.1 (K), D15.1 (K), D16.1 (K), U4.17 (PA7)
/KBD_L/KB_ROW_3: D19.1 (K), D20.1 (K), D21.1 (K), U4.29 (PA8)
/KBD_L/UART_RX: U4.31 (PA10), U6.4
/KBD_L/UART_TX: U4.30 (PA9), U5.2
/KBD_L/VBUS: D1.2 (A2), F1.1, USB1.2 (VBUS), USB1.11 (VBUS)
/KBD_R/KB_COL_0: SW17.1, SW18.1, SW22.1, SW29.1, U8.10 (PA0)
/KBD_R/KB_COL_1: SW23.1, SW24.1, SW25.1, SW33.1, U8.11 (PA1)
/KBD_R/KB_COL_2: SW26.1, SW27.1, SW28.1, SW37.1, U8.12 (PA2)
/KBD_R/KB_COL_3: SW30.1, SW31.1, SW32.1, U8.13 (PA3)
/KBD_R/KB_COL_4: SW34.1, SW35.1, SW36.1, U8.14 (PA4)
/KBD_R/KB_ROW_4: D17.1 (K), D23.1 (K), D26.1 (K), D30.1 (K), D34.1 (K), U8.15 (PA5)
/KBD_R/KB_ROW_5: D18.1 (K), D24.1 (K), D27.1 (K), D31.1 (K), D35.1 (K), U8.16 (PA6)
/KBD_R/KB_ROW_6: D22.1 (K), D25.1 (K), D28.1 (K), D32.1 (K), D36.1 (K), U8.17 (PA7)
/KBD_R/KB_ROW_7: D29.1 (K), D33.1 (K), D37.1 (K), U8.29 (PA8)
/KBD_R/UART_RX: U8.31 (PA10), U9.4
/KBD_R/UART_TX: U8.30 (PA9), U10.2
GND: D1.1 (A1), D38.1 (K), D39.1 (K), D40.1 (K), D41.1 (K), D42.1 (K), D43.1 (K), D44.1 (K), D45.1 (K), D46.1 (K), D47.1 (K), D48.1 (K), D49.1 (K), D50.1 (K), D51.1 (K), D52.1 (K), D53.1 (K), D54.1 (K), D55.1 (K), D56.1 (K), D57.1 (K), D58.1 (K), D59.1 (K), D60.1 (K), D61.1 (K), D62.1 (K), D63.1 (K), D64.1 (K), D65.1 (K), D66.1 (K), D67.1 (K), D68.1 (K), D69.1 (K), D70.1 (K), D71.1 (K), D72.1 (K), D73.1 (K), J1.1, J2.1, Q1.2 (S), Q2.2 (S), R1.2, R7.2, R13.2, R14.2, R51.2, R52.2, U1.1 (GND), U2.3 (GND), U2.8 (GND), U3.1, U3.3, U3.4, U4.8 (VSSA), U4.23 (VSS), U4.35 (VSS), U4.47 (VSS), U5.1, U5.3 (GND), U6.1, U6.3 (GND), U7.1, U7.3, U7.4, U8.8 (VSSA), U8.23 (VSS), U8.35 (VSS), U8.47 (VSS), U9.1, U9.3 (GND), U10.1, U10.3 (GND), USB1.1 (GND), USB1.12 (GND), USB1.13 (SHELL), USB1.14 (SHELL), Y1.2, Y1.4, Y2.2, Y2.4
unnamed: Audio1.1, R7.1
unnamed: Audio1.3, U5.4
unnamed: Audio1.4, U6.2
unnamed: Audio2.1, R14.1
unnamed: Audio2.3, U9.2
unnamed: Audio2.4, U10.4
unnamed: D2.2 (A), SW1.2
unnamed: D3.2 (A), SW3.2
unnamed: D4.2 (A), SW4.2
unnamed: D5.2 (A), SW5.2
unnamed: D6.2 (A), SW6.2
unnamed: D7.2 (A), SW7.2
unnamed: D8.2 (A), SW8.2
unnamed: D9.2 (A), SW9.2
unnamed: D10.2 (A), SW10.2
unnamed: D11.2 (A), SW11.2
unnamed: D12.2 (A), SW12.2
unnamed: D13.2 (A), SW13.2
unnamed: D14.2 (A), SW14.2
unnamed: D15.2 (A), SW15.2
unnamed: D16.2 (A), SW16.2
unnamed: D17.2 (A), SW17.2
unnamed: D18.2 (A), SW18.2
unnamed: D19.2 (A), SW19.2
unnamed: D20.2 (A), SW20.2
unnamed: D21.2 (A), SW21.2
unnamed: D22.2 (A), SW22.2
unnamed: D23.2 (A), SW23.2
unnamed: D24.2 (A), SW24.2
unnamed: D25.2 (A), SW25.2
unnamed: D26.2 (A), SW26.2
unnamed: D27.2 (A), SW27.2
unnamed: D28.2 (A), SW28.2
unnamed: D29.2 (A), SW29.2
unnamed: D30.2 (A), SW30.2
unnamed: D31.2 (A), SW31.2
unnamed: D32.2 (A), SW32.2
unnamed: D33.2 (A), SW33.2
unnamed: D34.2 (A), SW34.2
unnamed: D35.2 (A), SW35.2
unnamed: D36.2 (A), SW36.2
unnamed: D37.2 (A), SW37.2
unnamed: D38.2 (A), R15.2
unnamed: D39.2 (A), R16.2
unnamed: D40.2 (A), R17.2
unnamed: D41.2 (A), R23.2
unnamed: D42.2 (A), R22.2
unnamed: D43.2 (A), R20.2
unnamed: D44.2 (A), R18.2
unnamed: D45.2 (A), R19.2
unnamed: D46.2 (A), R27.2
unnamed: D47.2 (A), R28.2
unnamed: D48.2 (A), R21.2
unnamed: D49.2 (A), R26.2
unnamed: D50.2 (A), R25.2
unnamed: D51.2 (A), R24.2
unnamed: D52.2 (A), R32.2
unnamed: D53.2 (A), R31.2
unnamed: D54.2 (A), R30.2
unnamed: D55.2 (A), R29.2
unnamed: D56.2 (A), R34.2
unnamed: D57.2 (A), R35.2
unnamed: D58.2 (A), R50.2
unnamed: D59.2 (A), R41.2
unnamed: D60.2 (A), R40.2
unnamed: D61.2 (A), R39.2
unnamed: D62.2 (A), R42.2
unnamed: D63.2 (A), R49.2
unnamed: D64.2 (A), R48.2
unnamed: D65.2 (A), R43.2
unnamed: D66.2 (A), R38.2
unnamed: D67.2 (A), R37.2
unnamed: D68.2 (A), R44.2
unnamed: D69.2 (A), R47.2
unnamed: D70.2 (A), R46.2
unnamed: D71.2 (A), R45.2
unnamed: D72.2 (A), R36.2
unnamed: D73.2 (A), R33.2
unnamed: Q1.1 (G), R52.1, U8.26 (PB13)
unnamed: Q2.1 (G), R51.1, U4.26 (PB13)
unnamed: F1.2, U1.3 (VI)
unnamed: R2.2, U3.2, U4.7 (NRST)
unnamed: U4.5 (PD0), Y1.3
unnamed: U4.6 (PD1), Y1.1
unnamed: R8.2, U7.2, U8.7 (NRST)
unnamed: U8.5 (PD0), Y2.3
unnamed: U8.6 (PD1), Y2.1
unnamed: R1.1, USB1.4 (CC1)
unnamed: R13.1, USB1.10 (CC2)
